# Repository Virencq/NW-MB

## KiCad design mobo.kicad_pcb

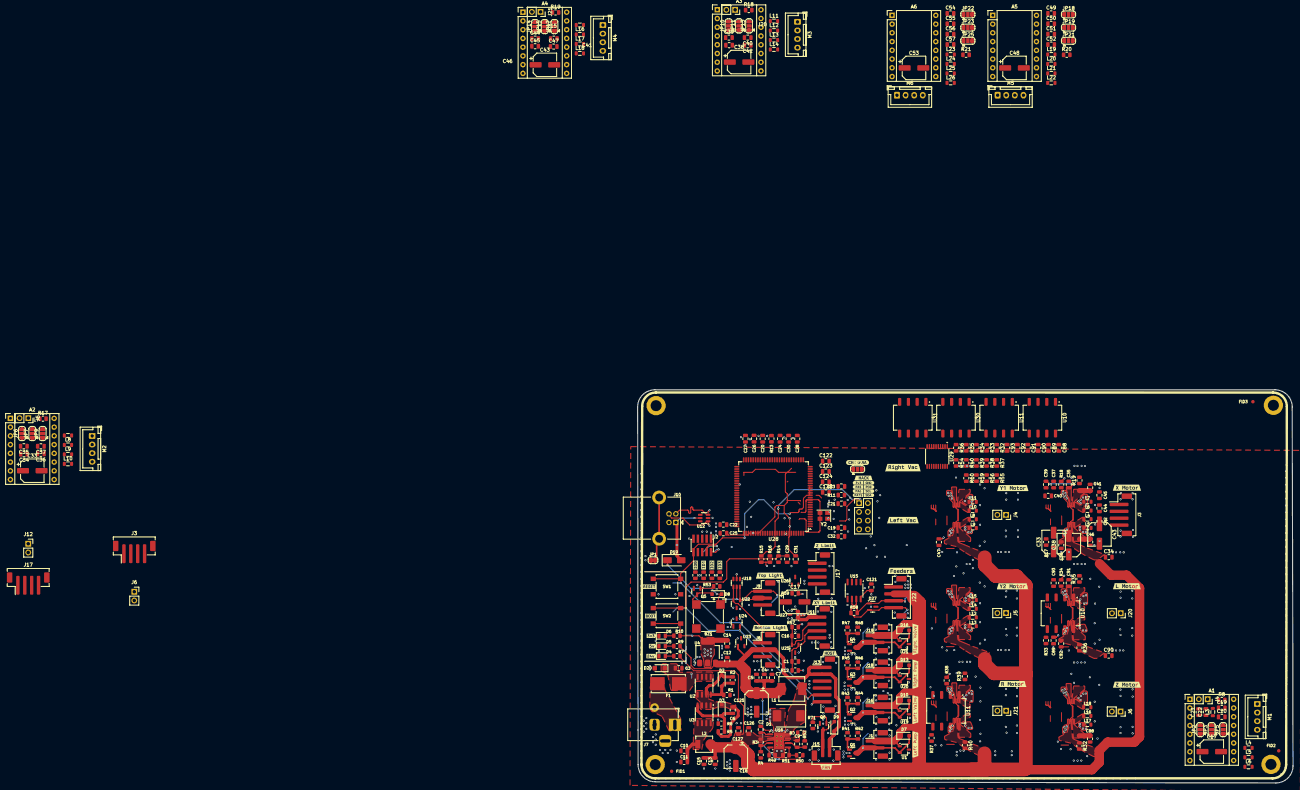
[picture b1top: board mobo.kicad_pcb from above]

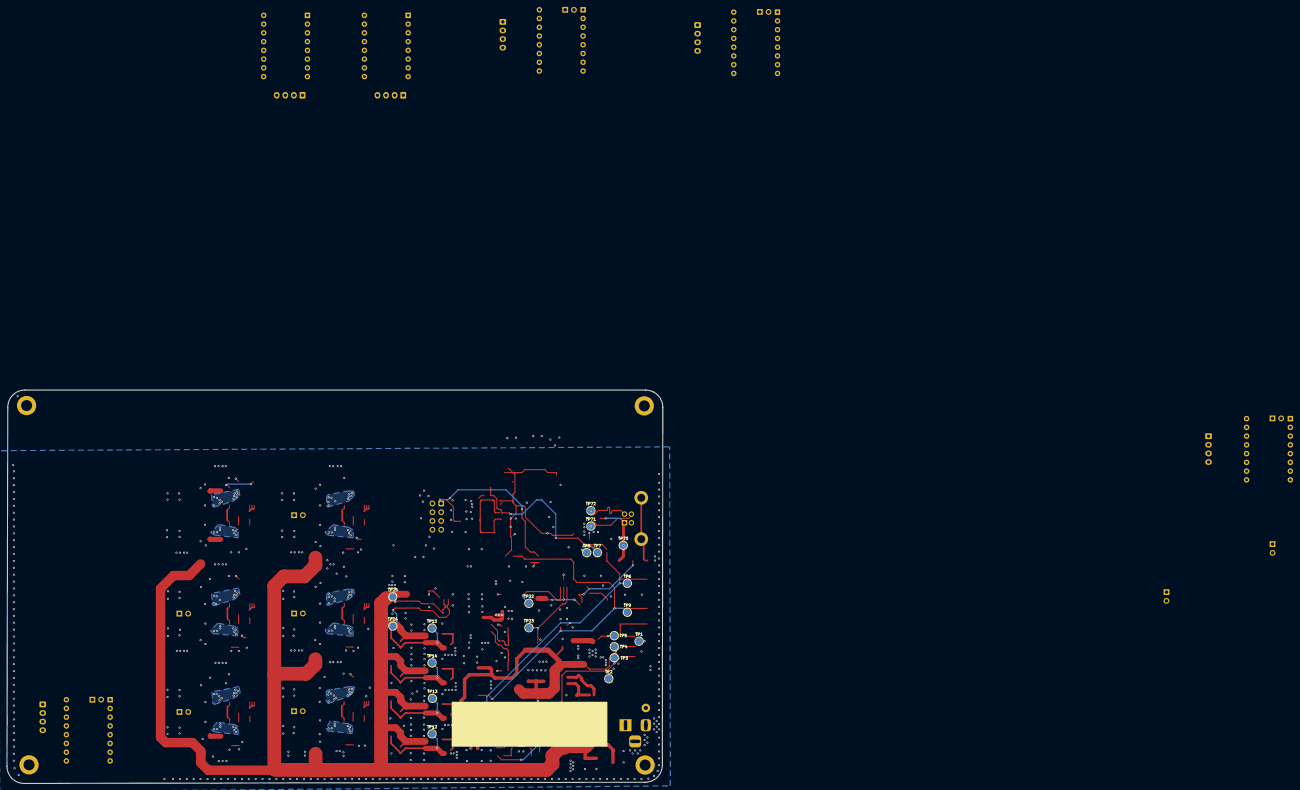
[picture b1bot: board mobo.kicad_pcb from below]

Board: 4 copper layers, 190.4 x 114.2 mm, 383 parts (20 on the bottom side), 159 nets.

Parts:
A1, A2, A3, A4, A5, A6: Motor_Driver; Pololu_Breakout-16_15.2x20.3mm
BZ1: Buzzer; MagneticBuzzer_CUI_CMT-8504-100-SMT
C1, C2, C6, C16, C23, C26, C27, C28, C29, C30, C31, C32, C88, C88#2, C90, C90#2, C91, C91#2, C92, C92#2, C93, C93#2, C121: 100n; C_0805_2012Metric
C3, C4, C5, C7, C10, C11, C12, C13, C14, C15, C126, C127: 10u; C_0805_2012Metric
C8: 4.7n; C_0805_2012Metric
C9: 47p; C_0805_2012Metric
C17, C17#2, C18, C33, C33#2, C38, C38#2, C43, C43#2, C48, C53, C125: 100u; CP_Elec_6.3x7.7
C19, C19#2, C20, C20#2, C21, C21#2, C22, C22#2, C34, C34#2, C35, C35#2, C36, C36#2, C37, C37#2, C39, C39#2, C40, C40#2, C41, C41#2, C42, C42#2, C44, C44#2, C45, C45#2, C46, C46#2, C47, C47#2, C49, C50, C51, C52, C54, C55, C56, C57: 1n; C_0805_2012Metric
C24, C25: 2.2u; C_0805_2012Metric
C89, C89#2: 22u; C_0805_2012Metric
C122, C123: 10p; C_0805_2012Metric
C124, C128: 2u2; C_0805_2012Metric
D1: B560C; D_SMC
D2, D3: BZT52C16; D_SOD-123
D4, D5, D6: Green; LED_0805_2012Metric
D7, D8, D9, D10, D13, D16: SM4007; D_SOD-123F
D19: SS34; D_SMA
D20: SMF28A; D_SMF
D27: SM712_SOT23; SOT-23
F1: Fuse; Fuseholder_Littelfuse_Nano2_154x
FID1, FID2, FID3: Fiducial; Fiducial_1mm_Mask2mm
H1, H2, H3, H4: MountingHole_Pad; MountingHole_3.2mm_M3_DIN965_Pad
J1, J16, J18, J19: FET; JST_PH_B2B-PH-SM4-TB_1x02-1MP_P2.00mm_Vertical
J2: SWD Header; PinHeader_2x05_P1.27mm_Vertical_SMD
J3, J3#2, J17, J17#2: MOTOR; JST_PH_B4B-PH-SM4-TB_1x04-1MP_P2.00mm_Vertical
J4, J4#2, J5, J5#2, J6, J6#2, J12, J20, J20#2, J21, J21#2: TMC_PIN_HEADER; PinSocket_1x02_P2.54mm_Vertical
J7: COMBO_POWER_JACK; BarrelJack_Horizontal
J8: BTM_LIGHT; JST_PH_B3B-PH-SM4-TB_1x03-1MP_P2.00mm_Vertical
J9: TOP_LIGHT; JST_PH_B3B-PH-SM4-TB_1x03-1MP_P2.00mm_Vertical
J10: USB_B; USB_B_Lumberg_2411_02_Horizontal
J11: XY_LIMIT; JST_PH_B4B-PH-SM4-TB_1x04-1MP_P2.00mm_Vertical
J13: HOST; JST_PH_B6B-PH-SM4-TB_1x06-1MP_P2.00mm_Vertical
J14: HACK_HEADER; PinHeader_2x04_P2.54mm_Vertical
J15: FAN; JST_PH_B2B-PH-SM4-TB_1x02-1MP_P2.00mm_Vertical
J22: FEEDERS; JST_PH_B4B-PH-SM4-TB_1x04-1MP_P2.00mm_Vertical
JP1: SHIELD_GND; SolderJumper-2_P1.3mm_Bridged_RoundedPad1.0x1.5mm
JP2, JP2#2, JP6, JP10, JP14, JP18, JP22: CFG0; SolderJumper-3_P1.3mm_Open_RoundedPad1.0x1.5mm
JP3, JP7, JP11, JP15, JP19, JP23: CFG1; SolderJumper-3_P1.3mm_Open_RoundedPad1.0x1.5mm
JP5, JP9, JP13, JP17, JP21, JP25: CFG3; SolderJumper-3_P1.3mm_Open_RoundedPad1.0x1.5mm
L1: 8.2uH; L_Sunlord_MWSA0603S
L2: 2.2u; L_Sunlord_MWSA0402S
L3, L4, L4#2, L5, L5#2, L6, L6#2, L7, L7#2, L8, L8#2, L9, L9#2, L10, L10#2, L11, L11#2, L12, L12#2, L13, L13#2, L14, L14#2, L15, L15#2, L16, L16#2, L17, L17#2, L18, L18#2, L19, L20, L21, L22, L23, L24, L25, L26: L_Ferrite; L_0805_2012Metric
M1, M2, M3, M4, M5, M6: Stepper_Motor; JST_XH_B4B-XH-A_1x04_P2.50mm_Vertical
Q1, Q2, Q3, Q4, Q5, Q6: AO3400A; SOT-23
R1, R3, R6, R7, R11, R12, R13, R14, R32, R32#2, R33, R33#2, R34, R34#2, R35, R35#2, R36, R36#2, R39, R39#2, R40, R40#2, R42, R44, R46, R48, R51, R54, R54#2, R55, R55#2, R57, R60: 10k; R_0805_2012Metric
R2, R4, R5, R9, R15, R16: 4.7k; R_0805_2012Metric
R8, R8#2, R10, R17, R17#2, R18, R18#2, R19, R19#2, R20, R21, R41, R43, R45, R47, R53, R71: 1k; R_0805_2012Metric
R37, R37#2, R38, R38#2, R56, R56#2, R59, R59#2: 4k7; R_0805_2012Metric
R49: 243k; R_0805_2012Metric
R50: 53.6k; R_0805_2012Metric
R52: 16.9k; R_0805_2012Metric
R58: 120; R_0805_2012Metric
SW1, SW2: SW_Push; SW_SPST_B3S-1000
TP1, TP2, TP3, TP4, TP5, TP6, TP7, TP8, TP9, TP12, TP13, TP14, TP15, TP22, TP23, TP24, TP25, TP70, TP71, TP72: TestPoint; TestPoint_Pad_D2.0mm
U1, U19, U20, U21: PESD24BS3; TSOT-23
U2, U3: FDS4435BZ; SO-8_3.9x4.9mm_P1.27mm
U4: AP1117-33; SOT-223-3_TabPin2
U10, U10#2, U11, U11#2, U30, U31: XGZP6857D; CFSensor_XGZP6897x
U12: SRV05-4; SOT-23-6
U15: MAX3078E; SOIC-8_3.9x4.9mm_P1.27mm
U16: TPS54560BDDA; Texas_R-PDSO-G8_EP2.95x4.9mm_Mask2.4x3.1mm_ThermalVias
U18: SN74LVC2G34; SOT-23-6
U22, U23: PESD5V2S2UT; SOT-23-3
U24, U25, U26, U27: PESD3V3S2UT; SOT-23-3
U28: STM32H723ZETx; LQFP-144_20x20mm_P0.5mm
U29: PCA9545A; TSSOP-20_4.4x6.5mm_P0.65mm
Y2: 8MHz; Crystal_SMD_3225-4Pin_3.2x2.5mm
kibuzzard-65DCF286: G***; kibuzzard-65DCF286
kibuzzard-65E24FAE: G***; kibuzzard-65E24FAE
kibuzzard-65E215D8: G***; kibuzzard-65E215D8
kibuzzard-65E215EC: G***; kibuzzard-65E215EC
kibuzzard-65E240B2: G***; kibuzzard-65E240B2
kibuzzard-65E241C9: G***; kibuzzard-65E241C9
kibuzzard-65E2151D: G***; kibuzzard-65E2151D
kibuzzard-65E2155B: G***; kibuzzard-65E2155B
kibuzzard-65E2156F: G***; kibuzzard-65E2156F
kibuzzard-65E2408C: G***; kibuzzard-65E2408C
kibuzzard-65E2409D: G***; kibuzzard-65E2409D
kibuzzard-65E2504F: G***; kibuzzard-65E2504F
kibuzzard-65E24108: G***; kibuzzard-65E24108
kibuzzard-65E24112: G***; kibuzzard-65E24112
kibuzzard-65E24141: G***; kibuzzard-65E24141
kibuzzard-65E25035: G***; kibuzzard-65E25035
kibuzzard-65E25071: G***; kibuzzard-65E25071
kibuzzard-65F1FEA3: G***; kibuzzard-65F1FEA3
kibuzzard-6585C0AF: G***; kibuzzard-6585C0AF
kibuzzard-6585C0D3: G***; kibuzzard-6585C0D3
kibuzzard-6585C08F: G***; kibuzzard-6585C08F
kibuzzard-6585C058: G***; kibuzzard-6585C058
kibuzzard-6606EA2E: G***; kibuzzard-6606EA2E
kibuzzard-6606EA4F: G***; kibuzzard-6606EA4F
kibuzzard-6606EA6E: G***; kibuzzard-6606EA6E
kibuzzard-65709CC6: G***; kibuzzard-65709CC6
kibuzzard-65709E62: G***; kibuzzard-65709E62
kibuzzard-65848E86: G***; kibuzzard-65848E86
kibuzzard-65848E91: G***; kibuzzard-65848E91
kibuzzard-65848EB6: G***; kibuzzard-65848EB6
kibuzzard-65848FCC: G***; kibuzzard-65848FCC
kibuzzard-65848FD5: G***; kibuzzard-65848FD5
kibuzzard-65848FDC: G***; kibuzzard-65848FDC
kibuzzard-65848FE3: G***; kibuzzard-65848FE3
kibuzzard-65848FE9: G***; kibuzzard-65848FE9
kibuzzard-65848FEF: G***; kibuzzard-65848FEF
kibuzzard-660711AC: G***; kibuzzard-660711AC
kibuzzard-66071149: G***; kibuzzard-66071149

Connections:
+3.3V: C14.1, C24.1, C25.1, C26.1, C27.1, C28.1, C30.1, C31.1, C32.1, C121.2, J2.1 (VTref), J11.1, J14.1, R10.1, R11.1, R12.2, R15.1, R16.1, R57.2, SW2.2, TP5.1, U4.2 (VO), U15.8 (VCC), U27.1, U27.2
+3V3: A1.2 (VDD), A1.14 (~SLEEP), A2.2 (VDD), A2.14 (~SLEEP), A3.2 (VDD), A3.14 (~SLEEP), A4.2 (VDD), A4.14 (~SLEEP), A5.2 (VDD), A5.14 (~SLEEP), A6.2 (VDD), A6.14 (~SLEEP), C88.1, C88#2.1, C89.1, C89#2.1, C90.1, C90#2.1, C91.1, C91#2.1, C92.1, C92#2.1, C93.1, C93#2.1, JP2.1 (A), JP2#2.1 (A), JP3.1 (A), JP5.1 (A), JP6.1 (A), JP7.1 (A), JP9.1 (A), JP10.1 (A), JP11.1 (A), JP13.1 (A), JP14.1 (A), JP15.1 (A), JP17.1 (A), JP18.1 (A), JP19.1 (A), JP21.1 (A), JP22.1 (A), JP23.1 (A), JP25.1 (A), R34.1, R34#2.1, R35.1, R35#2.1, R36.1, R36#2.1, R37.1, R37#2.1, R38.1, R38#2.1, R39.1, R39#2.1, R55.1, R55#2.1, R56.1, R56#2.1, R59.1, R59#2.1, R60.1, U10.2 (VDD), U10#2.2 (VDD), U11.2 (VDD), U11#2.2 (VDD), U28.6 (VBAT), U28.17 (VDD), U28.30 (VDD), U28.32 (VREF+), U28.39 (VDD), U28.52 (VDD), U28.62 (VDD), U28.72 (VDD), U28.84 (VDD), U28.108 (VDD), U28.121 (VDD), U28.131 (VDD), U28.144 (VDD), U29.20 (VDD), U30.2 (VDD), U31.2 (VDD)
+5V: BZ1.1 (+), C4.2, C5.2, C7.2, C12.1, C125.1, D8.1 (K), D9.1 (K), D19.1 (K), J8.2, J9.2, J13.1, J13.2, J15.1, L1.2, R9.1, R50.1, TP4.1, U4.3 (VI), U18.5 (VCC), U23.1
/Lighting/BTM_LIGHT: U18.3 (2A), U28.97 (PC7)
/Microcontroller/BOOT1: R13.1, U28.48 (PB2)
/Microcontroller/I2C_SCL: J14.6, R15.2, U29.18 (SCL)
/Microcontroller/I2C_SDA: J14.8, R16.2, U29.19 (SDA)
/Microcontroller/PD6: U28.119 (PD5), U28.122 (PD6)
/Microcontroller/PD14: U26.2, U28.85 (PD14)
/Microcontroller/SWCLK: J2.4 (SWCLK/TCK), TP7.1, U28.109 (PA14(JTCK)
/Microcontroller/SWDIO: J2.2 (SWDIO/TMS), TP8.1, U28.105 (PA13(JTMS)
/Microcontroller/USB_D+: J10.3 (D+), TP71.1, U12.1 (IO1), U28.104 (PA12)
/Microcontroller/USB_D-: J10.2 (D-), TP72.1, U12.3 (IO2), U28.103 (PA11)
/Microcontroller/X_LIMIT: C1.1, J11.3, R12.1, U25.1, U28.96 (PC6)
/Microcontroller/Y_LIMIT: C16.1, J11.2, R57.1, U25.2, U28.86 (PD15)
/Motor 1/1A: C20.1, C20#2.1, L4.2, L4#2.2, M1.2 (-)
/Motor 1/1B: C19.1, C19#2.1, L3.2, M1.1
/Motor 1/2A: C21.1, C21#2.1, L5.2, L5#2.2, M1.3
/Motor 1/2B: C22.1, C22#2.1, L6.2, L6#2.2, M1.4
/Motor 1/COPI: JP2.3 (B), JP2#2.3 (B)
/Motor 1/DIAG: J4.1, J4#2.1
/Motor 1/MS0: A1.10 (MS1), JP2.2 (C), JP2#2.2 (C)
/Motor 1/MS1: A1.11 (MS2), JP3.2 (C)
/Motor 1/MS2: R8.2, R8#2.2
/Motor 1/RESET: A1.13 (~RESET), JP5.2 (C)
/Motor 2/1A: C35.1, C35#2.1, L8.2, L8#2.2, M2.2 (-)
/Motor 2/1B: C34.1, C34#2.1, L7.2, L7#2.2, M2.1
/Motor 2/2A: C36.1, C36#2.1, L9.2, L9#2.2, M2.3
/Motor 2/2B: C37.1, C37#2.1, L10.2, L10#2.2, M2.4
/Motor 2/DIAG: J5.1, J5#2.1
/Motor 2/MS0: A2.10 (MS1), JP6.2 (C)
/Motor 2/MS1: A2.11 (MS2), JP7.2 (C)
/Motor 2/MS2: R17.2, R17#2.2
/Motor 2/RESET: A2.13 (~RESET), JP9.2 (C)
/Motor 3/1A: C40.1, C40#2.1, L12.2, L12#2.2, M3.2 (-)
/Motor 3/1B: C39.1, C39#2.1, L11.2, L11#2.2, M3.1
/Motor 3/2A: C41.1, C41#2.1, L13.2, L13#2.2, M3.3
/Motor 3/2B: C42.1, C42#2.1, L14.2, L14#2.2, M3.4
/Motor 3/DIAG: J20.1, J20#2.1
/Motor 3/MS0: A3.10 (MS1), JP10.2 (C)
/Motor 3/MS1: A3.11 (MS2), JP11.2 (C)
/Motor 3/MS2: R18.2, R18#2.2
/Motor 3/RESET: A3.13 (~RESET), JP13.2 (C)
/Motor 4/1A: C45.1, C45#2.1, L16.2, L16#2.2, M4.2 (-)
/Motor 4/1B: C44.1, C44#2.1, L15.2, L15#2.2, M4.1
/Motor 4/2A: C46.1, C46#2.1, L17.2, L17#2.2, M4.3
/Motor 4/2B: C47.1, C47#2.1, L18.2, L18#2.2, M4.4
/Motor 4/DIAG: J21.1, J21#2.1
/Motor 4/MS0: A4.10 (MS1), JP14.2 (C)
/Motor 4/MS1: A4.11 (MS2), JP15.2 (C)
/Motor 4/MS2: R19.2, R19#2.2
/Motor 4/RESET: A4.13 (~RESET), JP17.2 (C)
/Motor A/1A: C55.1, L24.2, M6.2 (-)
/Motor A/1B: C54.1, L23.2, M6.1
/Motor A/2A: C56.1, L25.2, M6.3
/Motor A/2B: C57.1, L26.2, M6.4
/Motor A/MS0: A6.10 (MS1), JP22.2 (C)
/Motor A/MS1: A6.11 (MS2), JP23.2 (C)
/Motor A/RESET: A6.13 (~RESET), JP25.2 (C)
/Motor Z/1A: C50.1, L20.2, M5.2 (-)
/Motor Z/1B: C49.1, L19.2, M5.1
/Motor Z/2A: C51.1, L21.2, M5.3
/Motor Z/2B: C52.1, L22.2, M5.4
/Motor Z/DIAG: J6.1, J6#2.1
/Motor Z/MS0: A5.10 (MS1), JP18.2 (C)
/Motor Z/MS1: A5.11 (MS2), JP19.2 (C)
/Motor Z/RESET: A5.13 (~RESET), JP21.2 (C)
/Motor_X/DIR: J17.2, J17#2.2
/Motor_X/EN: J17.3, J17#2.3
/Motor_X/STEP: J17.1, J17#2.1
/Motor_Y/DIR: J3.2, J3#2.2
/Motor_Y/EN: J3.3, J3#2.3
/Motor_Y/STEP: J3.1, J3#2.1
/Power/POWER_SUPPLY: F1.1, J7.1, J7.4
/Power/VIN: C3.2, D20.1 (A1), F1.2, TP2.1, U2.5 (D), U2.6 (D), U2.7 (D), U2.8 (D)
/RS485/RS-485+: D27.2 (A2), J22.4, R58.1, TP24.1, U15.6 (A)
/RS485/RS-485-: D27.1 (A1), J22.3, R58.2, TP25.1, U15.7 (B)
/Vacuum sensors/SC0: R37.2, R37#2.2, U10.5 (SCL), U10#2.5 (SCL), U29.6 (SC0)
/Vacuum sensors/SC1: R56.2, R56#2.2, U11.5 (SCL), U11#2.5 (SCL), U29.9 (SC1)
/Vacuum sensors/SD0: R38.2, R38#2.2, U10.4 (SDA), U10#2.4 (SDA), U29.5 (SD0)
/Vacuum sensors/SD1: R59.2, R59#2.2, U11.4 (SDA), U11#2.4 (SDA), U29.8 (SD1)
BOOT: C29.1, J13.5, R14.1, SW2.1, TP9.1, U24.2
GND: A1.1 (GND), A1.7 (GND), A2.1 (GND), A2.7 (GND), A3.1 (GND), A3.7 (GND), A4.1 (GND), A4.7 (GND), A5.1 (GND), A5.7 (GND), A6.1 (GND), A6.7 (GND), C1.2, C3.1, C4.1, C5.1, C7.1, C8.1, C9.1, C10.1, C11.1, C12.2, C13.1, C14.2, C15.1, C16.2, C17.2, C17#2.2, C18.2, C19.2, C19#2.2, C20.2, C20#2.2, C21.2, C21#2.2, C22.2, C22#2.2, C23.2, C24.2, C25.2, C26.2, C27.2, C28.2, C29.2, C30.2, C31.2, C32.2, C33.2, C33#2.2, C34.2, C34#2.2, C35.2, C35#2.2, C36.2, C36#2.2, C37.2, C37#2.2, C38.2, C38#2.2, C39.2, C39#2.2, C40.2, C40#2.2, C41.2, C41#2.2, C42.2, C42#2.2, C43.2, C43#2.2, C44.2, C44#2.2, C45.2, C45#2.2, C46.2, C46#2.2, C47.2, C47#2.2, C48.2, C49.2, C50.2, C51.2, C52.2, C53.2, C54.2, C55.2, C56.2, C57.2, C88.2, C88#2.2, C89.2, C89#2.2, C90.2, C90#2.2, C91.2, C91#2.2, C92.2, C92#2.2, C93.2, C93#2.2, C121.1, C122.2, C123.2, C124.2, C125.2, C126.1, C127.1, C128.2, D1.2 (A), D4.1 (K), D5.1 (K), D6.1 (K), D20.2 (A2), D27.3 (common), H1.1, H2.1, H3.1, H4.1, J1.MP (MountPin), J2.3 (GND), J2.5 (GND), J2.9 (GNDDetect), J3.4, J3.MP (MountPin), J3#2.4, J3#2.MP (MountPin), J7.2, J7.3, J8.3, J8.MP (MountPin), J9.3, J9.MP (MountPin), J10.4 (GND), J11.4, J11.MP (MountPin), J13.3, J13.4, J13.MP (MountPin), J14.2, J15.MP (MountPin), J16.MP (MountPin), J17.4, J17.MP (MountPin), J17#2.4, J17#2.MP (MountPin), J18.MP (MountPin), J19.MP (MountPin), J22.1, J22.MP (MountPin), JP1.2 (B), Q1.2 (S), Q2.2 (S), Q3.2 (S), Q4.2 (S), Q5.2 (S), Q6.2 (S), R1.2, R4.2, R6.2, R13.2, R14.2, R42.1, R44.1, R46.1, R48.1, R49.2, R51.2, SW1.1, TP1.1, U1.3, U4.1 (GND), U10.6 (GND), U10#2.6 (GND), U11.6 (GND), U11#2.6 (GND), U12.2 (VN), U15.5 (GND), U16.7 (GND), U16.9 (GND), U18.2 (GND), U19.3, U20.3, U21.3, U22.3, U23.3, U24.3, U25.3, U26.3, U27.3, U28.16 (VSS), U28.31 (VSSA), U28.38 (VSS), U28.51 (VSS), U28.61 (VSS), U28.83 (VSS), U28.94 (VSS), U28.107 (VSS), U28.120 (VSS), U28.130 (VSS), U29.1 (A0), U29.2 (A1), U29.10 (VSS), U30.6 (GND), U31.6 (GND), Y2.2, Y2.4
unnamed: A1.4 (1A), L4.1, L4#2.1
unnamed: A1.3 (1B), L3.1
unnamed: A1.5 (2A), L5.1, L5#2.1
unnamed: A1.6 (2B), L6.1, L6#2.1
unnamed: A1.12 (MS3), R8.1, R8#2.1
unnamed: A2.4 (1A), L8.1, L8#2.1
unnamed: A2.3 (1B), L7.1, L7#2.1
unnamed: A2.5 (2A), L9.1, L9#2.1
unnamed: A2.6 (2B), L10.1, L10#2.1
unnamed: A2.12 (MS3), R17.1, R17#2.1
unnamed: A3.4 (1A), L12.1, L12#2.1
unnamed: A3.3 (1B), L11.1, L11#2.1
unnamed: A3.5 (2A), L13.1, L13#2.1
unnamed: A3.6 (2B), L14.1, L14#2.1
unnamed: A3.12 (MS3), R18.1, R18#2.1
unnamed: A4.4 (1A), L16.1, L16#2.1
unnamed: A4.3 (1B), L15.1, L15#2.1
unnamed: A4.5 (2A), L17.1, L17#2.1
unnamed: A4.6 (2B), L18.1, L18#2.1
unnamed: A4.12 (MS3), R19.1, R19#2.1
unnamed: A5.4 (1A), L20.1
unnamed: A5.3 (1B), L19.1
unnamed: A5.5 (2A), L21.1
unnamed: A5.6 (2B), L22.1
unnamed: A5.12 (MS3), R20.1
unnamed: A6.4 (1A), L24.1
unnamed: A6.3 (1B), L23.1
unnamed: A6.5 (2A), L25.1
unnamed: A6.6 (2B), L26.1
unnamed: A6.12 (MS3), R21.1
unnamed: BZ1.2 (-), D8.2 (A), Q5.3 (D)
unnamed: C8.2, R52.2
unnamed: C10.2, C11.2, L2.1, U3.5 (D), U3.6 (D), U3.7 (D), U3.8 (D)
unnamed: C2.1, D1.1 (K), L1.1, U16.8 (SW)
unnamed: D2.2 (A), R1.1, R2.2, U2.4 (G)
unnamed: C6.2, D2.1 (K), D3.1 (K), R2.1, R5.1, U2.1 (S), U2.2 (S), U2.3 (S), U3.1 (S), U3.2 (S), U3.3 (S)
unnamed: C6.1, D3.2 (A), R5.2, R6.1, U3.4 (G)
unnamed: D4.2 (A), R7.2
unnamed: D5.2 (A), R9.2
unnamed: D6.2 (A), R10.2
unnamed: D7.2 (A), J1.2, Q1.3 (D), TP12.1, U1.2
unnamed: D9.2 (A), J15.2, Q6.3 (D)
unnamed: D10.2 (A), J16.2, Q2.3 (D), TP13.1, U19.2
unnamed: D13.2 (A), J18.2, Q3.3 (D), TP14.1, U20.2
unnamed: D16.2 (A), J19.2, Q4.3 (D), TP15.1, U21.2
unnamed: J8.1, TP23.1, U18.4 (2Y), U22.2
unnamed: J9.1, TP22.1, U18.6 (1Y), U22.1
unnamed: J10.5 (Shield), JP1.1 (A)
unnamed: Q1.1 (G), R41.1, R42.2
unnamed: Q2.1 (G), R43.1, R44.2
unnamed: Q3.1 (G), R45.1, R46.2
unnamed: Q4.1 (G), R47.1, R48.2
unnamed: Q5.1 (G), R53.2
unnamed: Q6.1 (G), R71.2
unnamed: C2.2, U16.1 (BOOT)
unnamed: C9.2, R52.1, U16.6 (COMP)
unnamed: R3.2, R4.1, U16.3 (EN)
unnamed: R50.2, R51.1, U16.5 (FB)
unnamed: R49.1, U16.4 (RT/CLK)
unnamed: C123.1, U28.138 (BOOT0), Y2.3
unnamed: C122.1, U28.25 (NRST), Y2.1
unnamed: C124.1, U28.23 (PH0)
unnamed: C128.1, U28.24 (PH1)
unnamed: R40.2, R40#2.2, U29.13 (SC2)
unnamed: R32.2, R32#2.2, U29.16 (SC3)
unnamed: R54.2, R54#2.2, U29.12 (SD2)
unnamed: R33.2, R33#2.2, U29.15 (SD3)
unnamed: R34.2, R34#2.2, U29.4 (_INT0_)
unnamed: R55.2, R55#2.2, U29.7 (_INT1_)
unnamed: R60.2, U29.11 (_INT2_)
unnamed: R39.2, R39#2.2, U29.14 (_INT3_)
unnamed: R36.2, R36#2.2, U29.17 (_INT_)
unnamed: R35.2, R35#2.2, U29.3 (_RESET_)
RESET: C23.1, J2.10 (~RESET), J13.6, R11.2, SW1.2, TP6.1, U24.1
VBUS: D19.2 (A), J10.1 (VBUS), TP70.1, U12.5 (VP)
VDC: A1.8 (VMOT), A2.8 (VMOT), A3.8 (VMOT), A4.8 (VMOT), A5.8 (VMOT), A6.8 (VMOT), C13.2, C15.2, C17.1, C17#2.1, C18.1, C33.1, C33#2.1, C38.1, C38#2.1, C43.1, C43#2.1, C48.1, C53.1, C126.2, C127.2, D7.1 (K), D10.1 (K), D13.1 (K), D16.1 (K), J1.1, J16.1, J18.1, J19.1, J22.2, L2.2, R3.1, R7.1, TP3.1, U1.1, U16.2 (VIN), U19.1, U20.1, U21.1
